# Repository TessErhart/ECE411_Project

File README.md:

# ECE411 Project 2018
Group 2
Team members: Tess Erhart, Jennifer Lara, Brandon Barber, and Martin Rodriguez

# Word Clock

Concept: Rather than displaying the time like a traditional clock, this clock uses LEDs to light words on a panel, “spelling out” the time.

Inspiration:<br/>
<https://www.amazon.com/LED-Word-Clock-Displays-Powered/dp/B00JPNWR3G><br/>
<https://www.instructables.com/id/Wordclock/>

/datasheets: Contains all relevant datasheets<br/>
/docs: Contains all relevant documents, schematics, layouts, testing plans, etc.<br/>
/rtc_ds3231: Contains all code<br/>
/schematics: Contains all schematics and layouts<br/>

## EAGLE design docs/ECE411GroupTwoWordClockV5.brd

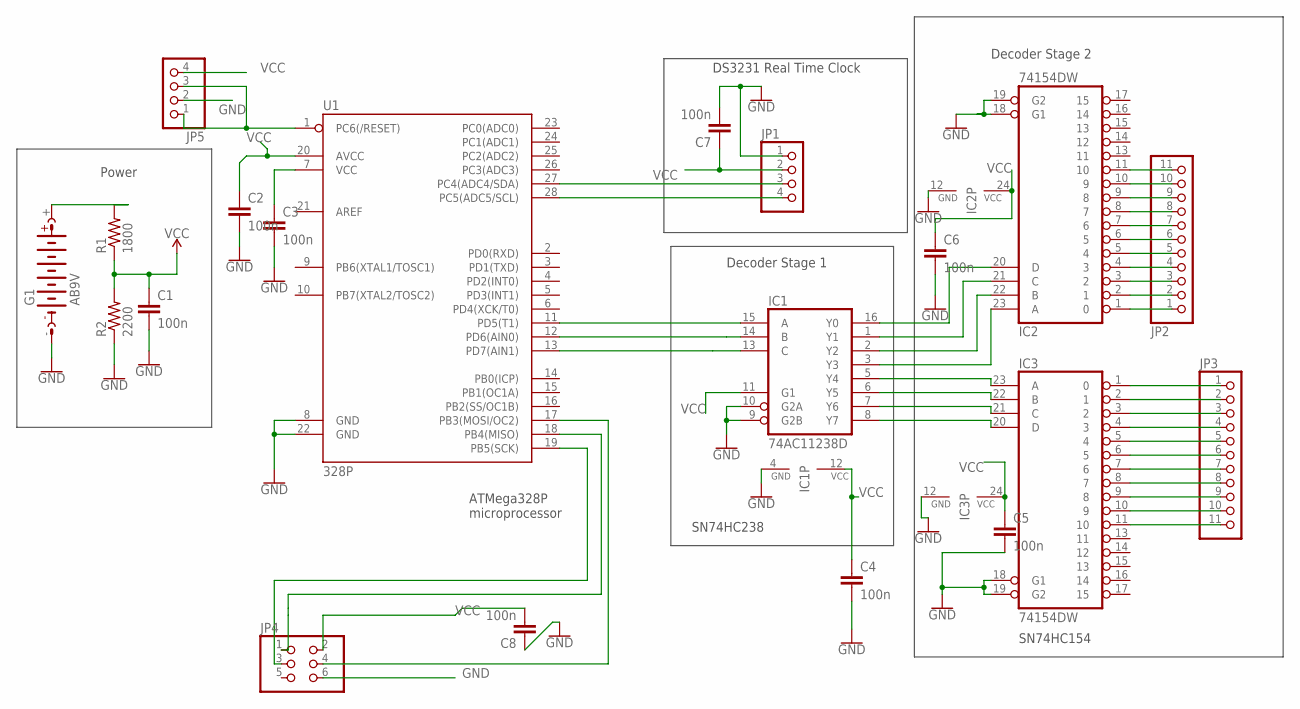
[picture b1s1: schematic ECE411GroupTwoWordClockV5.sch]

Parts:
C1, C2, C3, C4, C5, C6, C7, C8: 100n; C025-025X050
G1: AB9V
IC1: 74AC11238D; SO16
IC2, IC3: 74154DW; SO24W
JP1, JP5: PINHD-1X4; 1X04
JP2, JP3: PINHD-1X11; 1X11
JP4: PINHD-2X3; 2X03
R1: 1800; 0204V
R2: 2200; 0204V
U1: 328P; DIP28

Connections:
GND: C1.2, C2.2, C3.2, C4.2, C5.2, C6.2, C7.2, C8.1, G1.-, IC1.4 (GND), IC1.9 (G2B), IC1.10 (G2A), IC2.12 (GND), IC2.18 (G1), IC2.19 (G2), IC3.12 (GND), IC3.18 (G1), IC3.19 (G2), JP1.1, JP4.6, JP5.2, R2.1, U1.8 (GND), U1.22 (GND)
unnamed: G1.+, R1.2
unnamed: JP1.4, U1.28 (PC5(ADC5/SCL))
unnamed: JP1.3, U1.27 (PC4(ADC4/SDA))
unnamed: IC1.15 (A), U1.11 (PD5(T1))
unnamed: C3.1, U1.7 (VCC)
unnamed: IC1.13 (C), U1.13 (PD7(AIN1))
unnamed: IC1.3 (Y3), IC2.23 (A)
unnamed: IC1.2 (Y2), IC2.22 (B)
unnamed: IC1.1 (Y1), IC2.21 (C)
unnamed: IC1.16 (Y0), IC2.20 (D)
unnamed: IC2.1 (0), JP2.1
unnamed: IC2.2 (1), JP2.2
unnamed: IC2.3 (2), JP2.3
unnamed: IC2.4 (3), JP2.4
unnamed: IC2.5 (4), JP2.5
unnamed: IC1.14 (B), U1.12 (PD6(AIN0))
unnamed: IC2.6 (5), JP2.6
unnamed: IC2.7 (6), JP2.7
unnamed: IC2.8 (7), JP2.8
unnamed: IC2.9 (8), JP2.9
unnamed: IC2.10 (9), JP2.10
unnamed: IC1.5 (Y4), IC3.23 (A)
unnamed: IC1.6 (Y5), IC3.22 (B)
unnamed: IC1.7 (Y6), IC3.21 (C)
unnamed: IC3.1 (0), JP3.1
unnamed: IC1.8 (Y7), IC3.20 (D)
unnamed: IC3.2 (1), JP3.2
unnamed: IC3.3 (2), JP3.3
unnamed: IC3.4 (3), JP3.4
unnamed: IC3.5 (4), JP3.5
unnamed: IC3.6 (5), JP3.6
unnamed: IC3.7 (6), JP3.7
unnamed: IC3.8 (7), JP3.8
unnamed: IC3.9 (8), JP3.9
unnamed: IC3.10 (9), JP3.10
unnamed: IC3.11 (10), JP3.11
unnamed: IC2.11 (10), JP2.11
unnamed: JP4.1, U1.18 (PB4(MISO))
unnamed: JP4.3, U1.19 (PB5(SCK))
unnamed: JP4.4, U1.17 (PB3(MOSI/OC2))
unnamed: JP5.1, JP5.3, U1.1 (PC6(/RESET))
VCC: C1.1, C2.1, C4.1, C5.1, C6.1, C7.1, C8.2, IC1.11 (G1), IC1.12 (VCC), IC2.24 (VCC), IC3.24 (VCC), JP1.2, JP4.2, JP5.4, R1.1, R2.2, U1.20 (AVCC)

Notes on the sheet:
Power
ATMega328P microprocessor
DS3231 Real Time Clock
Decoder Stage 1
Decoder Stage 2
SN74HC154
SN74HC238

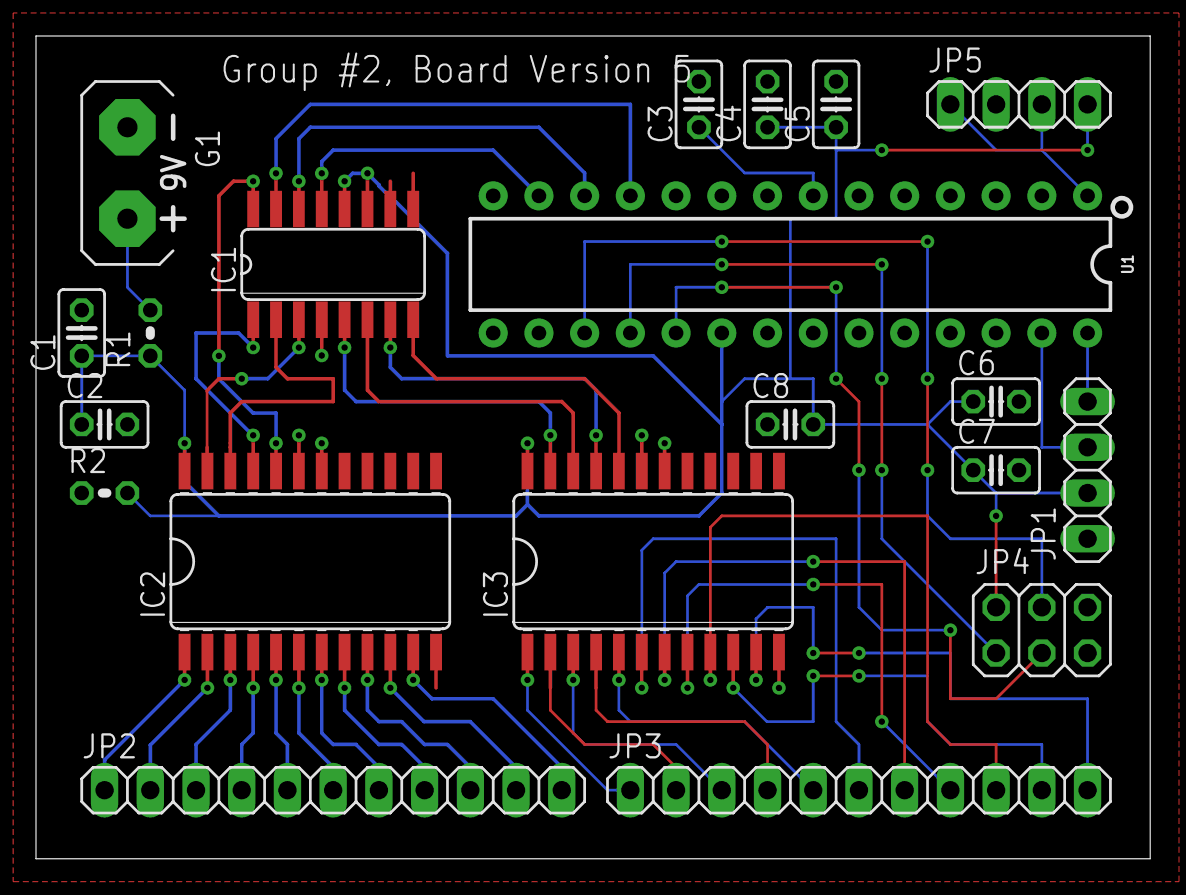
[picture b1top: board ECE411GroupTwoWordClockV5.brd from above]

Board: 2 copper layers, 61.9 x 45.7 mm, 20 parts (0 on the bottom side), 43 nets.

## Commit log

2018-09-29 Create LICENSE
2018-10-25 Schematics
2018-11-06 Add files via upload
    This was our first version of the schematic for the circuit/PCB
2018-11-13 Add datatsheets and group's PDS to /docs.
2018-11-14 Start work on faceplate. Add helpful links doc and faceplate templates for use with acrylic
2018-11-14 Rearranged files
2018-11-14 reorganized (or tried to)
2018-12-03 Library Used
    I'll add where I got it from later but this is the library I used to set the time on the DS3231
2018-12-04 Add files to docs
2018-12-05 Add files via upload (#1)
    * Add files via upload
    * Library Used
    I'll add where I got it from later but this is the library I used to set the time on the DS3231
    * Add files via upload
    * Add files via upload

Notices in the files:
parts and their libraries:
SparkFun-IC-Microcontroller: Licensing: Creative Commons ShareAlike 4.0 International - https://creativecommons.org/licenses/by-sa/4.0
